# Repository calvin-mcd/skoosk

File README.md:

# skoosk

some kind of ortholinear split keyboard

The skoosk was my first attempt at creating a split ortholinear keyboard from scratch. The first production run had some issues with the pcb and the plate files. In the process of rectifying these issues I ended up creating simplifying the pcb for manual assembly. There are two different types of switch and backplates. One for more bounce, the other for more stability.

## Layout

<a href="https://www.keyboard-layout-editor.com/#/gists/cdc0d16012a44037b1bdb8499f2bf92a">Link<a>

## Pictures

## Project Files

*skoosk pcb rgb* is not designed for manual assembly supporting LEDs and a reset switch if wanted.

*skoosk switchplate & backplate 4 screwholes* each have 4 outer screwholes that give the sandwhich assembly a good amount of bounce.

*skoosk switchplate & backplate 8 screwholes* have 8 screwholes in total to offer more stability for the whole sandwhich case.

## Todo
- [ ] test newest pcb revision
- [ ] add firmware support for the RGB indicator leds

## Disclaimer

Please note that this project has not been tested in its final version. There are no guarantees of a working outcome. No-one involved in this project is responsible for any usage issues that may arise. However, feel free to edit, modify and otherwise utilise these files.

## License

This project is released under the GPL v3 License. Please refer to the LICENCE file.

## Credits

As always big thanks to the many people who helped me with the pcb, firmware and much more! 

Any questions, contact Calvin#0563 on Discord.

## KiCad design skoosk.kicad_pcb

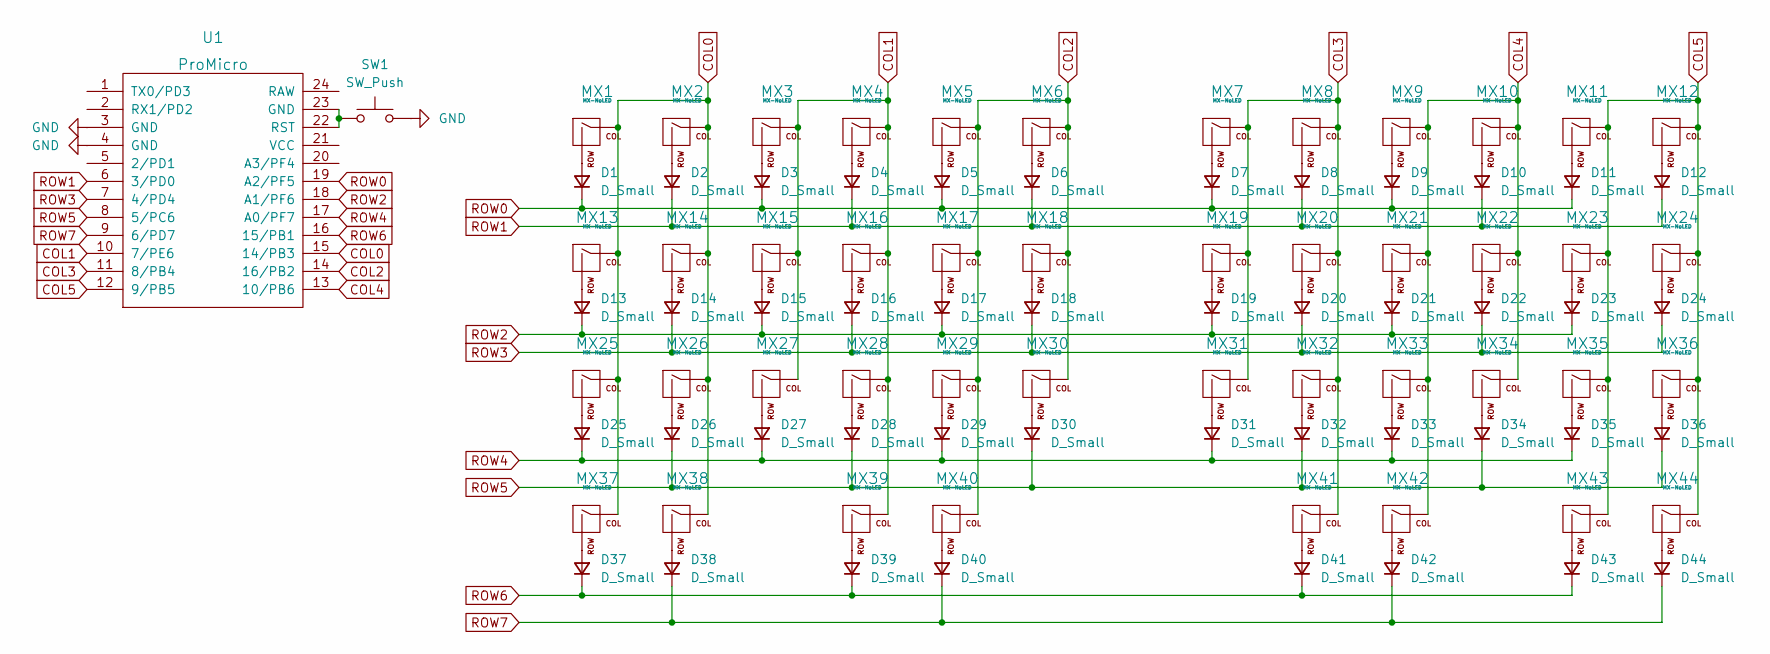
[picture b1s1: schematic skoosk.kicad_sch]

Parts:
D1, D2, D3, D4, D5, D6, D7, D8, D9, D10, D11, D12, D13, D14, D15, D16, D17, D18, D19, D20, D21, D22, D23, D24, D25, D26, D27, D28, D29, D30, D31, D32, D33, D34, D35, D36, D37, D38, D39, D40, D41, D42, D43, D44: D_Small; D_DO-35_SOD27_P7.62mm_Horizontal
MX1, MX12, MX13, MX24, MX25, MX36, MX37, MX38, MX39, MX42, MX43, MX44: MX-NoLED; MXOnly-1.25U-NoLED
MX2, MX3, MX4, MX5, MX6, MX7, MX8, MX9, MX10, MX11, MX14, MX15, MX16, MX17, MX18, MX19, MX20, MX21, MX22, MX23, MX26, MX27, MX28, MX29, MX30, MX31, MX32, MX33, MX34, MX35: MX-NoLED; MXOnly-1U-NoLED
MX40, MX41: MX-NoLED; MXOnly-3U-NoLED
SW1: SW_Push; SKQG-1155865
U1: ProMicro; ArduinoProMicro

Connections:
COL0: MX1.1 (COL), MX2.1 (COL), MX13.1 (COL), MX14.1 (COL), MX25.1 (COL), MX26.1 (COL), MX37.1 (COL), MX38.1 (COL), U1.15 (14/PB3)
COL1: MX3.1 (COL), MX4.1 (COL), MX15.1 (COL), MX16.1 (COL), MX27.1 (COL), MX28.1 (COL), MX39.1 (COL), U1.10 (7/PE6)
COL2: MX5.1 (COL), MX6.1 (COL), MX17.1 (COL), MX18.1 (COL), MX29.1 (COL), MX30.1 (COL), MX40.1 (COL), U1.14 (16/PB2)
COL3: MX7.1 (COL), MX8.1 (COL), MX19.1 (COL), MX20.1 (COL), MX31.1 (COL), MX32.1 (COL), MX41.1 (COL), U1.11 (8/PB4)
COL4: MX9.1 (COL), MX10.1 (COL), MX21.1 (COL), MX22.1 (COL), MX33.1 (COL), MX34.1 (COL), MX42.1 (COL), U1.13 (10/PB6)
COL5: MX11.1 (COL), MX12.1 (COL), MX23.1 (COL), MX24.1 (COL), MX35.1 (COL), MX36.1 (COL), MX43.1 (COL), MX44.1 (COL), U1.12 (9/PB5)
GND: SW1.2, U1.3 (GND), U1.4 (GND)
unnamed: D1.2 (A), MX1.2 (ROW)
unnamed: D2.2 (A), MX2.2 (ROW)
unnamed: D3.2 (A), MX3.2 (ROW)
unnamed: D4.2 (A), MX4.2 (ROW)
unnamed: D5.2 (A), MX5.2 (ROW)
unnamed: D6.2 (A), MX6.2 (ROW)
unnamed: D7.2 (A), MX7.2 (ROW)
unnamed: D8.2 (A), MX8.2 (ROW)
unnamed: D9.2 (A), MX9.2 (ROW)
unnamed: D10.2 (A), MX10.2 (ROW)
unnamed: D11.2 (A), MX11.2 (ROW)
unnamed: D12.2 (A), MX12.2 (ROW)
unnamed: D13.2 (A), MX13.2 (ROW)
unnamed: D14.2 (A), MX14.2 (ROW)
unnamed: D15.2 (A), MX15.2 (ROW)
unnamed: D16.2 (A), MX16.2 (ROW)
unnamed: D17.2 (A), MX17.2 (ROW)
unnamed: D18.2 (A), MX18.2 (ROW)
unnamed: D19.2 (A), MX19.2 (ROW)
unnamed: D20.2 (A), MX20.2 (ROW)
unnamed: D21.2 (A), MX21.2 (ROW)
unnamed: D22.2 (A), MX22.2 (ROW)
unnamed: D23.2 (A), MX23.2 (ROW)
unnamed: D24.2 (A), MX24.2 (ROW)
unnamed: D25.2 (A), MX25.2 (ROW)
unnamed: D26.2 (A), MX26.2 (ROW)
unnamed: D27.2 (A), MX27.2 (ROW)
unnamed: D28.2 (A), MX28.2 (ROW)
unnamed: D29.2 (A), MX29.2 (ROW)
unnamed: D30.2 (A), MX30.2 (ROW)
unnamed: D31.2 (A), MX31.2 (ROW)
unnamed: D32.2 (A), MX32.2 (ROW)
unnamed: D33.2 (A), MX33.2 (ROW)
unnamed: D34.2 (A), MX34.2 (ROW)
unnamed: D35.2 (A), MX35.2 (ROW)
unnamed: D36.2 (A), MX36.2 (ROW)
unnamed: D37.2 (A), MX37.2 (ROW)
unnamed: D38.2 (A), MX38.2 (ROW)
unnamed: D39.2 (A), MX39.2 (ROW)
unnamed: D40.2 (A), MX40.2 (ROW)
unnamed: D41.2 (A), MX41.2 (ROW)
unnamed: D42.2 (A), MX42.2 (ROW)
unnamed: D43.2 (A), MX43.2 (ROW)
unnamed: D44.2 (A), MX44.2 (ROW)
unnamed: SW1.1, U1.22 (RST), U1.23 (GND)
ROW0: D1.1 (K), D3.1 (K), D5.1 (K), D7.1 (K), D9.1 (K), D11.1 (K), U1.19 (A2/PF5)
ROW1: D2.1 (K), D4.1 (K), D6.1 (K), D8.1 (K), D10.1 (K), D12.1 (K), U1.6 (3/PD0)
ROW2: D13.1 (K), D15.1 (K), D17.1 (K), D19.1 (K), D21.1 (K), D23.1 (K), U1.18 (A1/PF6)
ROW3: D14.1 (K), D16.1 (K), D18.1 (K), D20.1 (K), D22.1 (K), D24.1 (K), U1.7 (4/PD4)
ROW4: D25.1 (K), D27.1 (K), D29.1 (K), D31.1 (K), D33.1 (K), D35.1 (K), U1.17 (A0/PF7)
ROW5: D26.1 (K), D28.1 (K), D30.1 (K), D32.1 (K), D34.1 (K), D36.1 (K), U1.8 (5/PC6)
ROW6: D37.1 (K), D39.1 (K), D41.1 (K), D43.1 (K), U1.16 (15/PB1)
ROW7: D38.1 (K), D40.1 (K), D42.1 (K), D44.1 (K), U1.9 (6/PD7)

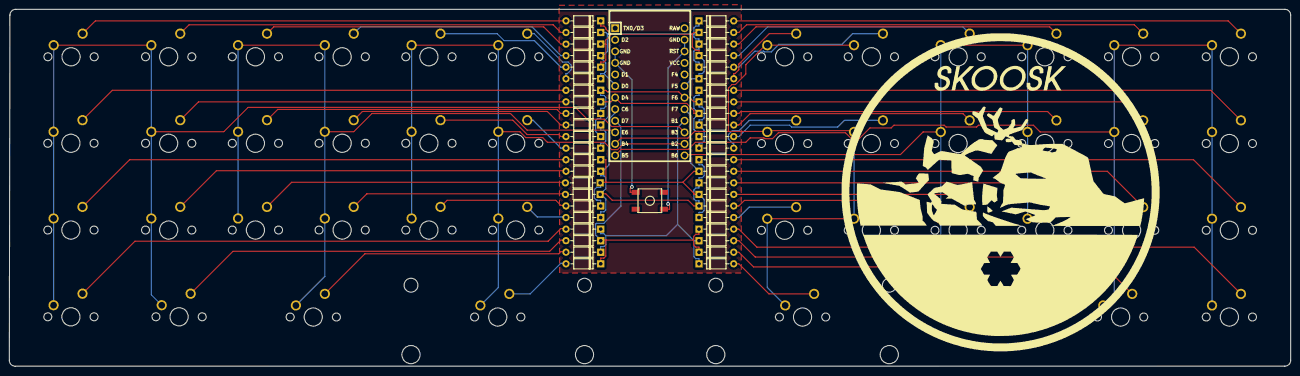
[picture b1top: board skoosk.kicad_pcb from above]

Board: 2 copper layers, 281.4 x 78.4 mm, 92 parts (1 on the bottom side), 60 nets.

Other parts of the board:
Gback: LOGO
Gfront: LOGO

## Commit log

2022-09-29 Add submodules
2022-09-29 adding libraries
2022-09-29 switch matrix build, footprints layed out
    missing is MCU footprint, reset switch, traces
    do i want underglow?
2022-09-29 all switches and diodes placed
    next change mcu for usb c, figure out a reset button
2022-09-29 tracing col and rows
2022-09-30 saving before doing autorouting
2022-09-30 added silkscreen, protective layer, auto tracing
    auto tracing still needs to be confirmed working
2022-09-30 zero error return
    add some led?
    get feedback?
2022-09-30 GND filling done, added some ideas
    maybe a rotary encoder and rgd leds?
2022-10-01 ordering schematics to add rotary and rgd
2022-10-01 added rotary and rgb to schematics and editor
    not yet fully confirmed to be working correctly
2022-10-01 rotary schematics updated, smd capacitors chosen for rgb
2022-10-01 fixed schematics
    new routing to be done
2022-10-01 final fix to schematic
    noah approved
2022-10-02 completed schematics & pcb
    no error messages
2022-10-02 first draft, no mounting holes
2022-10-06 changed layout for pcb, switch and backplate. added curved routes
2022-10-06 mounting holes added
2022-10-06 cleaned switchplate, added holes to pcb and backplate
2022-10-07 finalising pcb, backplate, switchplate. cleaning up redundant files
2022-10-08 cleaned up pcb and switchplate
2022-10-08 cleaning things up
2022-10-09 created gerbers for pcb, switch and backplate
2022-10-11 generated gerbers, tried to fill in parts
2022-10-15 backup update
2022-10-20 cleaned up pcb, switch & backplate
2022-10-24 cleaning up
    changed pcb size, for mounting
    flipped stabs on plate and pcb
    changed clearance on copper fill
2022-10-25 pcb, plate edge cuts changed
2022-10-25 zero drc errors, gerber, drill created
2022-10-25 created production files for all parts
    parts list stilll missing
2022-10-26 created jlc production files
2022-11-08 fixed plates with v1.1, slight rerouting for visual consistency on pcb
2022-11-10 v1.1
2022-11-21 cleaned up plate files and options
2022-11-26 repairing schematics, changing pcb
2022-12-17 clean up
2022-12-22 update skoosk
2022-12-22 added image folder
2023-01-10 readme update
2023-01-10 readme update, delete license
2023-01-11 backup
2023-07-10 single pcb version, simplifying project
